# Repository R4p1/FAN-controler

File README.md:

# FAN-controler

## Overview
- Design of controller for verification of general-purpose 4-pin fan

## Requirement
### Development
- KiCad8.0

## Usage
- Writing a program to arduino nano.
- Connect arduino nano, 4-pin fan and 12VDC power supply.
- PWM duty ratio can be changed by pressing the button.
- RPM and pwm duty ratio can be monitored.
(pwm frequency:25kHz)
(Recommended power supply:12V, 1A)

## Features
- Use to check operation of 4-pin fan

## Author
- [R4p1](https://github.com/R4p1)

## License
- (C) 2024 R4p1

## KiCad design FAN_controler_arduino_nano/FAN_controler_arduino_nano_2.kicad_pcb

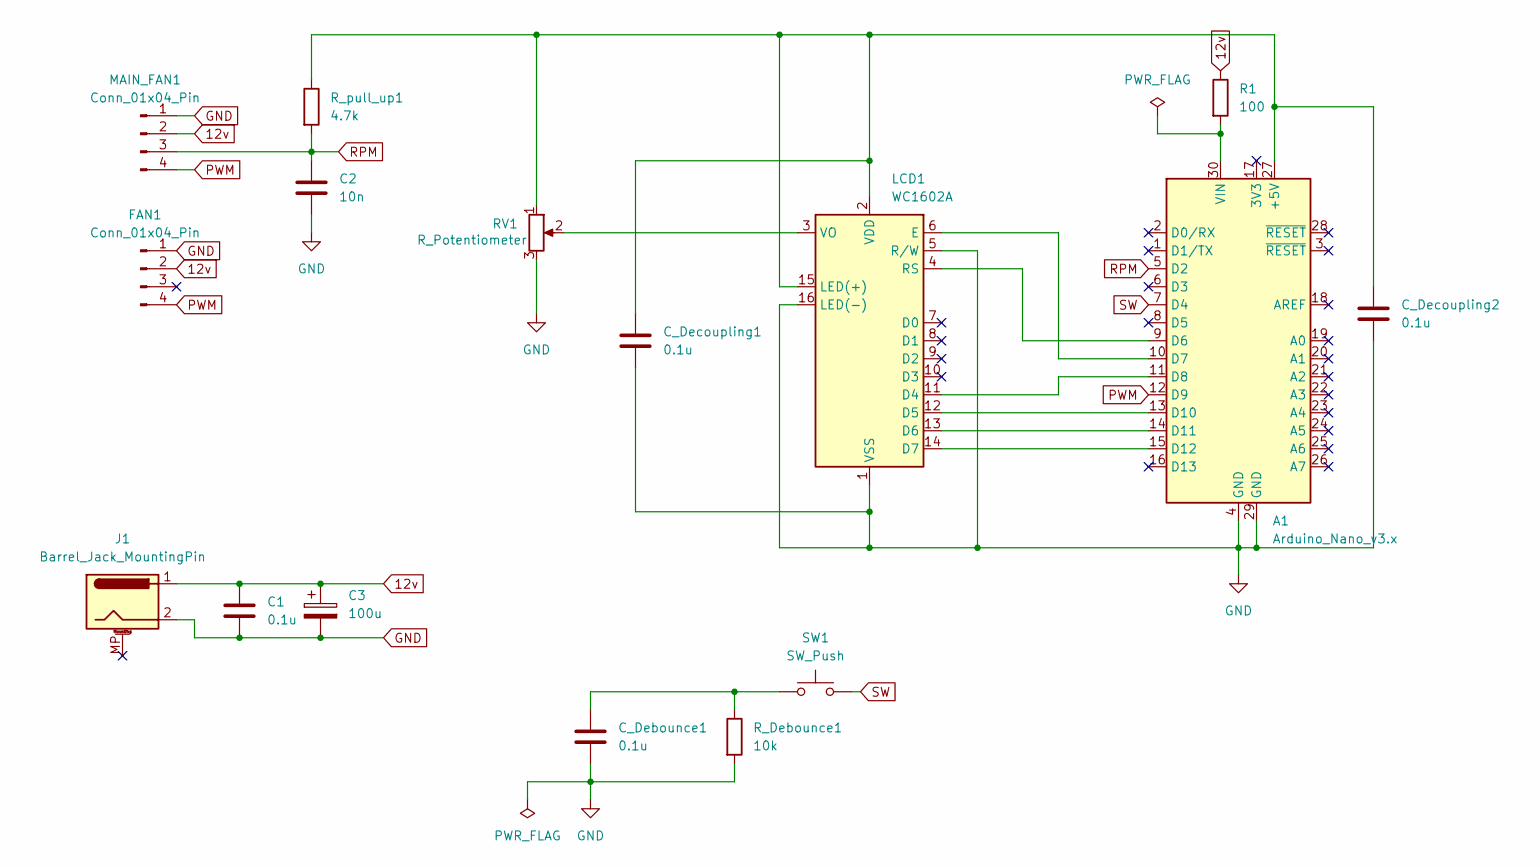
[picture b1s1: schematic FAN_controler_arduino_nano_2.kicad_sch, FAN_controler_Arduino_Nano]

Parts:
A1: Arduino_Nano_v3.x; Arduino_Nano
C1: 0.1u; C_0603_1608Metric_Pad1.08x0.95mm_HandSolder
C2: 10n; C_0603_1608Metric_Pad1.08x0.95mm_HandSolder
C3: 100u; CP_Radial_D5.0mm_P2.50mm
C_Debounce1: 0.1u; C_0603_1608Metric_Pad1.08x0.95mm_HandSolder
C_Decoupling1, C_Decoupling2: 0.1u; C_0603_1608Metric_Pad1.08x0.95mm_HandSolder
FAN1: Conn_01x04_Pin; FanPinHeader_1x04_P2.54mm_Vertical
J1: Barrel_Jack_MountingPin; BarrelJack_Horizontal
LCD1: WC1602A
MAIN_FAN1: Conn_01x04_Pin; FanPinHeader_1x04_P2.54mm_Vertical
R1: 100; R_0603_1608Metric_Pad0.98x0.95mm_HandSolder
RV1: R_Potentiometer; Potentiometer_Bourns_3296W_Vertical
R_Debounce1: 10k; R_0603_1608Metric_Pad0.98x0.95mm_HandSolder
R_pull_up1: 4.7k; R_0603_1608Metric_Pad0.98x0.95mm_HandSolder
SW1: SW_Push; SW_PUSH_6mm_H5mm

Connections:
12v: C1.1, C3.1, FAN1.2, J1.1, MAIN_FAN1.2, R1.1
GND: A1.4 (GND), A1.29 (GND), C1.2, C2.2, C3.2, C_Debounce1.2, C_Decoupling1.2, C_Decoupling2.2, FAN1.1, J1.2, LCD1.1 (VSS), LCD1.5 (R/W), LCD1.16 (LED(-)), MAIN_FAN1.1, RV1.3, R_Debounce1.2
unnamed: A1.27 (+5V), C_Decoupling1.1, C_Decoupling2.1, LCD1.2 (VDD), LCD1.15 (LED(+)), RV1.1, R_pull_up1.1
unnamed: A1.9 (D6), LCD1.4 (RS)
unnamed: A1.10 (D7), LCD1.6 (E)
unnamed: A1.11 (D8), LCD1.11 (D4)
unnamed: A1.13 (D10), LCD1.12 (D5)
unnamed: A1.14 (D11), LCD1.13 (D6)
unnamed: A1.15 (D12), LCD1.14 (D7)
unnamed: A1.30 (VIN), R1.2
unnamed: C_Debounce1.1, R_Debounce1.1, SW1.1
unnamed: LCD1.3 (VO), RV1.2
PWM: A1.12 (D9), FAN1.4, MAIN_FAN1.4
RPM: A1.5 (D2), C2.1, MAIN_FAN1.3, R_pull_up1.2
SW: A1.7 (D4), SW1.2

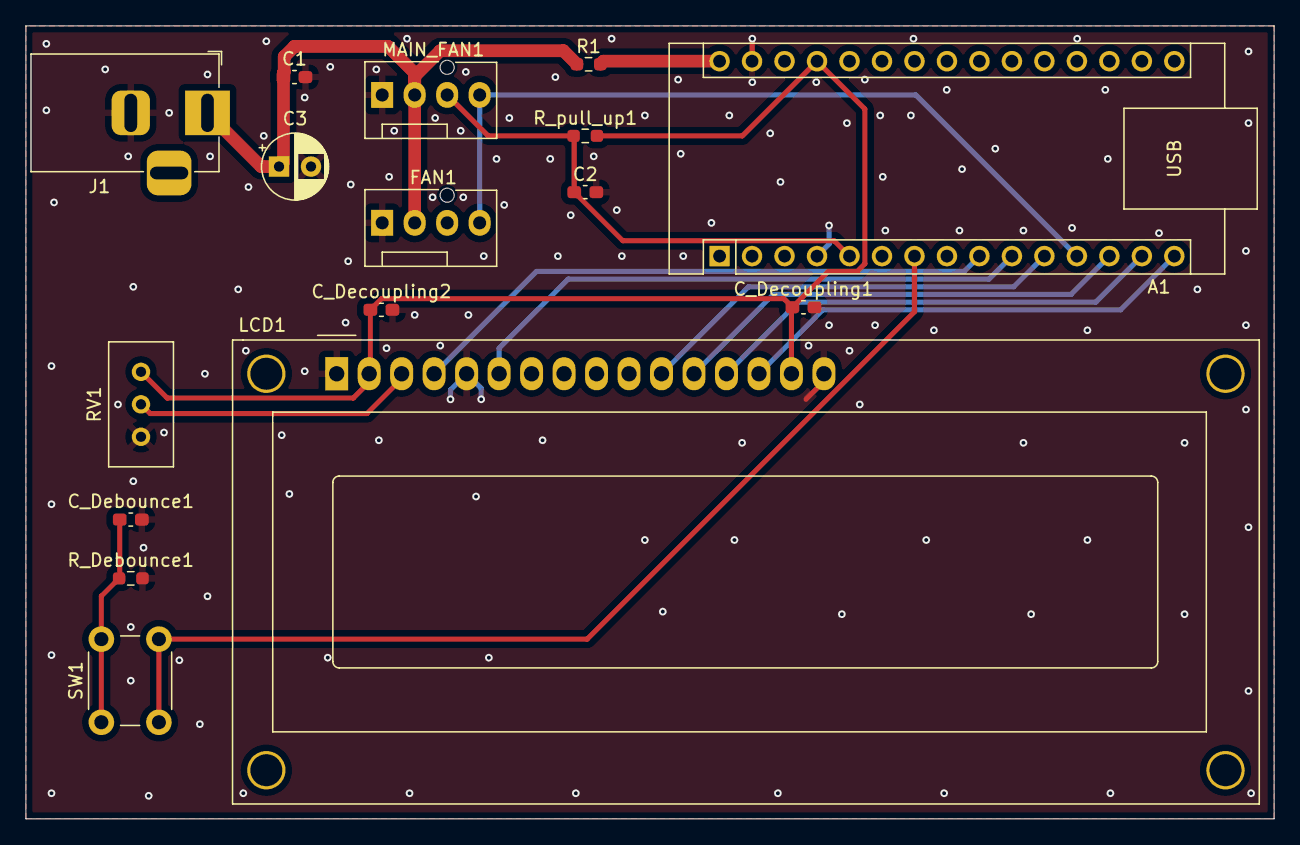
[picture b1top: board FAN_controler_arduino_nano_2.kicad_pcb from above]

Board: 2 copper layers, 97.6 x 62.0 mm, 16 parts (0 on the bottom side), 15 nets.

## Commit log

2024-11-06 upload FAN-controler-board KiCad file
2024-11-07 Update parts-list
